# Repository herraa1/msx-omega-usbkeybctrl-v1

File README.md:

# MSX Omega Home Computer USB Keyboard Controller PCB v1a

This is a rebuild of [Censlab's USB-keyboard-to-OMEGA-converter](https://github.com/Censlab/USB-keyboard-to-OMEGA-converter) using KiCad with some slight modifications.

> [!Note]
> Sillicony became Censlab on January 2024.

## Introduction

Censlab provides (thanks!) both the firmware and gerber files of his USB-keyboard-to-OMEGA-converter free for non-commercial use under the [cc-by-sa-4.0](https://creativecommons.org/licenses/by-sa/4.0/) license.

But if you need to make slight modifications to the adapter (mecanical tweaks, component size changes, connector additions, etc.) the gerber files are not suitable.
As the adapter hardware is small and with a few components, I decided to rebuild the adapter using KiCad to facilitate my own and future modifications.

## [Hardware](hardware/kicad/)

The original USB-keyboard-to-OMEGA-converter from Censlab is designed to snap directly to the Omega Computer keyboard port, thus it doesn't include installation holes.

| |
|:--|
| Original USB-keyboard-to-OMEGA-converter from Censlab |

The adapter rebuild presented here adds the following minor modifications:
* generic installation holes (marked red in the image below)
  * can be used to attach the USB keyboard converter board anywhere
* specific two-hole configuration (marked green in the image below) to attach the USB keyboard converter board to the Omega Home Computer using two of the right side Omega main board holes
  * this simplifies installing the USB keyboard converter board on the Omega Home Computer when it collides with an internal CX-2 floppy drive controller HAT
* USB connector header (marked blue in the image below) that uses the same pinout of a PC USB header
  * this header enables the use of generic USB cables with panel mount USB connectors to easily bring the USB port to the outside of the computer case
  * this may be specially useful as the adapter is now compatible with several computers ([Omega](https://github.com/skiselev/omega), [JFF](https://github.com/konkotgit/JFF))
* silkscreen includes values for all components
* SMD component footprint sizes have been changed to 1206 to make manual soldering easier

||
|:--|
| Modified USB Keyboard Controller |

## [Firmware](https://github.com/Censlab/USB-keyboard-to-OMEGA-converter/tree/main/elf)

This board uses the unmodified firmware provided by Censlab (thanks!) to implement the keyboard controller.

## Example installation on the Omega Home Computer main PCB

## References

Censlab USB-keyboard-to-OMEGA-converter
* https://github.com/Censlab/USB-keyboard-to-OMEGA-converter

MSX Makers! OMEGA USB KEYB CTRL build instructions
* https://msxmakers.design.blog/proyectos/omega-usb-keyb-ctrl/

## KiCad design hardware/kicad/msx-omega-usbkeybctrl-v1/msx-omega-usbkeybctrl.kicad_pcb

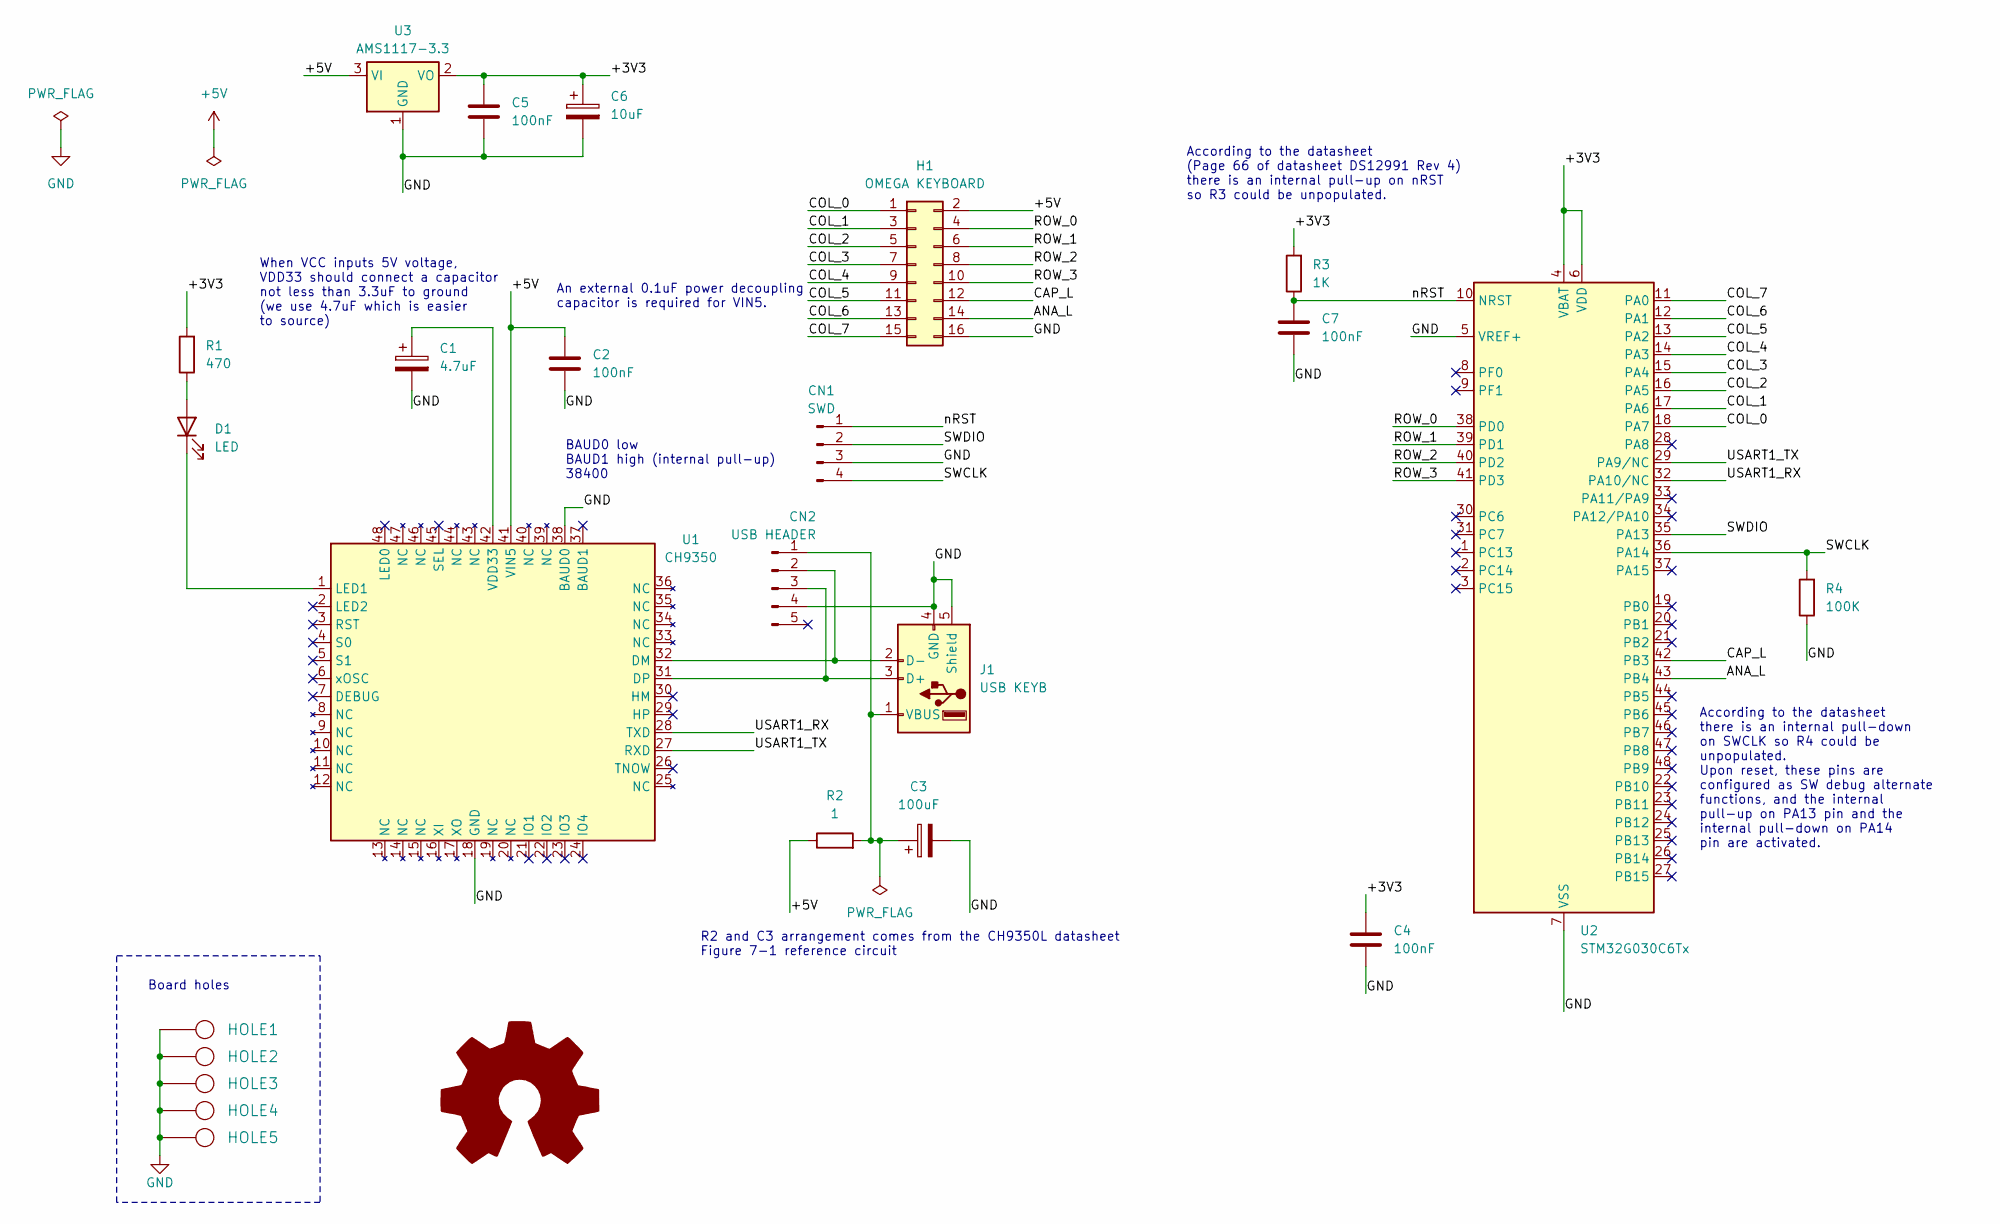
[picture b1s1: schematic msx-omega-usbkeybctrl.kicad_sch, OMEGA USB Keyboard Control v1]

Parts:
C1: 4.7uF; C_1206_3216Metric_Pad1.33x1.80mm_HandSolder
C2, C4, C5, C7: 100nF; C_1206_3216Metric_Pad1.33x1.80mm_HandSolder
C3: 100uF; CP_EIA-3216-18_Kemet-A_Pad1.58x1.35mm_HandSolder
C6: 10uF; C_1206_3216Metric_Pad1.33x1.80mm_HandSolder
CN1: SWD; PinHeader_1x04_P2.54mm_Vertical
CN2: USB HEADER; PinHeader_1x05_P2.54mm_Vertical
D1: LED; LED_1206_3216Metric_Pad1.42x1.75mm_HandSolder
H1: OMEGA KEYBOARD; IDC-Header_2x08_P2.54mm_Vertical
HOLE1, HOLE2, HOLE3, HOLE4, HOLE5: HOLE; Hole_3mm
J1: USB KEYB; USB_A_CONNFLY_DS1095-WNR0
R1: 470; R_1206_3216Metric_Pad1.30x1.75mm_HandSolder
R2: 1; R_1206_3216Metric_Pad1.30x1.75mm_HandSolder
R3: 1K; R_1206_3216Metric_Pad1.30x1.75mm_HandSolder
R4: 100K; R_1206_3216Metric_Pad1.30x1.75mm_HandSolder
SYM1: Logo_Open_Hardware_Large; OSHW-Logo_7.5x8mm_SilkScreen
U1: CH9350; LQFP-48_7x7mm_P0.5mm
U2: STM32G030C6Tx; LQFP-48_7x7mm_P0.5mm
U3: AMS1117-3.3; SOT-223-3_TabPin2

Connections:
+5V: C2.1, H1.2, R2.1, U1.41 (VIN5), U3.3 (VI)
/+3V3: C4.1, C5.1, C6.1, R1.2, R3.2, U2.4 (VBAT), U2.6 (VDD), U3.2 (VO)
/ANA_L: H1.14, U2.43 (PB4)
/CAP_L: H1.12, U2.42 (PB3)
/COL_0: H1.1, U2.18 (PA7)
/COL_1: H1.3, U2.17 (PA6)
/COL_2: H1.5, U2.16 (PA5)
/COL_3: H1.7, U2.15 (PA4)
/COL_4: H1.9, U2.14 (PA3)
/COL_5: H1.11, U2.13 (PA2)
/COL_6: H1.13, U2.12 (PA1)
/COL_7: H1.15, U2.11 (PA0)
/ROW_0: H1.4, U2.38 (PD0)
/ROW_1: H1.6, U2.39 (PD1)
/ROW_2: H1.8, U2.40 (PD2)
/ROW_3: H1.10, U2.41 (PD3)
/SWCLK: CN1.4, R4.2, U2.36 (PA14)
/SWDIO: CN1.2, U2.35 (PA13)
/USART1_RX: U1.28 (TXD), U2.32 (PA10/NC)
/USART1_TX: U1.27 (RXD), U2.29 (PA9/NC)
/nRST: C7.2, CN1.1, R3.1, U2.10 (NRST)
GND: C1.2, C2.2, C3.2, C4.2, C5.2, C6.2, C7.1, CN1.3, CN2.4, H1.16, HOLE1.1, HOLE2.1, HOLE3.1, HOLE4.1, HOLE5.1, J1.4 (GND), J1.5 (Shield), R4.1, U1.18 (GND), U1.38 (BAUD0), U2.5 (VREF+), U2.7 (VSS), U3.1 (GND)
unnamed: C3.1, CN2.1, J1.1 (VBUS), R2.2
unnamed: CN2.2, J1.2 (D-), U1.32 (DM)
unnamed: CN2.3, J1.3 (D+), U1.31 (DP)
unnamed: D1.2 (A), R1.1
unnamed: D1.1 (K), U1.1 (LED1)
unnamed: C1.1, U1.42 (VDD33)

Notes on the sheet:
According to the datasheet there is an internal pull-down on SWCLK so R4 could be unpopulated. Upon reset, these pins are configured as SW debug alternate functions, and the internal pull-up on PA13 pin and the internal pull-down on PA14 pin are activated.
BAUD0 low BAUD1 high (internal pull-up) 38400
R2 and C3 arrangement comes from the CH9350L datasheet Figure 7-1 reference circuit
An external 0.1uF power decoupling capacitor is required for VIN5.
When VCC inputs 5V voltage, VDD33 should connect a capacitor not less than 3.3uF to ground (we use 4.7uF which is easier to source)
Board holes
According to the datasheet (Page 66 of datasheet DS12991 Rev 4) there is an internal pull-up on nRST so R3 could be unpopulated.

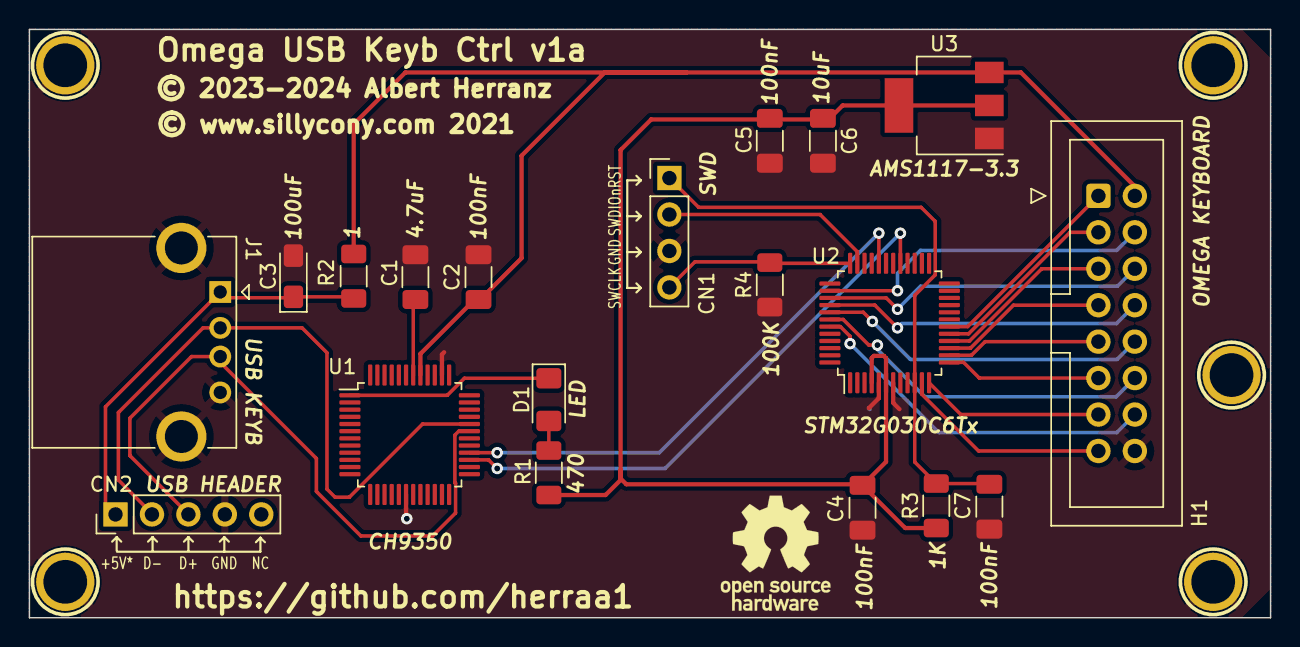
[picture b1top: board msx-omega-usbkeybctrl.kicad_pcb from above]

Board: 2 copper layers, 86.5 x 41.0 mm, 25 parts (0 on the bottom side), 28 nets.

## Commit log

2024-01-07 Initial commit for v1a
2024-01-28 add readme and gerbers
2024-01-28 Added same license as original project
2024-03-17 fix wrong year

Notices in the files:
hardware/kicad/msx-omega-usbkeybctrl-v1/msx-omega-usbkeybctrl.kicad_pcb:
© 2023-2024 Albert Herranz
© www.sillycony.com 2021
